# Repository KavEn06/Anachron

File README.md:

<h1 align="center">Anachron</h1>

<p align="center"><b>A smart pocket watch.</b></p>

<p align="center">
  ESP32-S3 &nbsp;·&nbsp; 1.46" round touch display &nbsp;·&nbsp; haptics &nbsp;·&nbsp; rotary crown &nbsp;·&nbsp; USB-C charging &nbsp;·&nbsp; 45 mm 4-layer PCB
</p>

Anachron is a smart pocket watch: an extension of your phone that does what a smartwatch does, but lives in your pocket instead of on your wrist. The idea comes from the same place as people going back to wired headphones.

Everything sits on one round PCB sized to match the display. An ESP32-S3 drives a 412 × 412 round touch screen, a rotary encoder with a push button behind it acts as the crown, a haptic motor gives feedback, and a LiPo cell charges over USB-C. This repository holds the electronics, designed in KiCad 10, and renders of the enclosure, modeled in Fusion 360.

## Contents

- [Concept](#concept)
- [Hardware](#hardware)
- [Why these parts](#why-these-parts)
- [The board](#the-board)
- [PCB layers](#pcb-layers)
- [Schematics](#schematics)
- [Pin map](#pin-map)
- [Power budget](#power-budget)
- [Firmware notes](#firmware-notes)
- [Bill of materials](#bill-of-materials)
- [Enclosure](#enclosure)
- [Working with the project](#working-with-the-project)

## Concept

The original sketch describes a pocket watch or keychain with several faces that connects to a phone over Bluetooth LE. The plan was for it to:

- show notifications from the phone
- control music with the crown and two programmable buttons
- work as a normal pocket watch, with the time and a timer
- switch between faces, including a Tamagotchi-style one and a CD-style one for Spotify
- use the IMU to wake up and to feed features on those faces

The shape in the sketch is the one the board follows: a round touch screen, a crown at the top with a button either side, and a USB-C port at the bottom for charging and flashing. The haptic motor, a "maybe" in the sketch, made it onto the board.

## Hardware

| Block | Part | Details |
| --- | --- | --- |
| MCU | ESP32-S3-WROOM-1-N8R8 | Dual-core 240 MHz, Wi-Fi and Bluetooth LE, 8 MB flash, 8 MB PSRAM, native USB |
| Display | Waveshare 1.46inch Touch LCD Module | Round IPS, 412 × 412, SPD2010 controller. Display over QSPI, touch over I2C (address `0x53`), on an 18-pin 0.5 mm flat-flex cable |
| Motion | Bosch BMI270 | 6-axis IMU on I2C (address `0x69`), both interrupt pins wired, used for wake and gesture detection |
| Haptics | TITAN Drake motor + MAX98357A | The I2S amplifier drives the motor through the `MP1` pads; gain is set by a solder jumper |
| Crown | Alps EC05 rotary encoder + C&K PTS845 | The encoder has no switch of its own, so a push button sits behind it in line with the shaft |
| Side buttons | 2 × C&K PTS845 | Left and right. All three buttons share one ADC pin through a resistor ladder |
| Timekeeping | 32.768 kHz crystal (Seiko SC-32S) | No separate RTC chip: the time is synced from the phone and the crystal keeps it in between |
| Charging | MCP73831 | Single-cell charger at 212 mA with a charge LED |
| Power path | AO3401A + SM5817 | Runs from USB when plugged in, from the battery otherwise |
| Regulator | AP2112K-3.3 | 600 mA, 3.3 V LDO, enabled by the `SYS PWR` solder jumper |
| USB | GCT USB4520 USB-C | USB 2.0 for flashing, with USBLC6-2SC6 ESD protection |
| Battery | 802035 LiPo, 400 to 550 mAh | Has its own protection circuit, plugs into a JST-PH connector, voltage measured through a divider |

```mermaid
flowchart LR
    USB["USB-C"] -->|VBUS| CHG["MCP73831 charger"]
    CHG --> BAT["LiPo cell"]
    USB -->|"VBUS through SM5817"| VSYS(("VSYS"))
    BAT -->|"AO3401A"| VSYS
    VSYS --> LDO["AP2112K 3.3 V"]
    LDO --> MCU["ESP32-S3-WROOM-1"]
    USB <-->|"USB data"| MCU
    MCU <-->|QSPI| LCD["1.46 inch round LCD"]
    MCU <-->|I2C| TOUCH["Touch"]
    MCU <-->|I2C| IMU["BMI270"]
    MCU -->|I2S| AMP["MAX98357A"]
    AMP --> OUT["Haptic motor"]
    ENC["Crown encoder"] --> MCU
    BTN["3 buttons"] -->|ADC| MCU
    XTAL["32.768 kHz crystal"] --- MCU
```

## Why these parts

- **Display:** the 1.46" round panel has the highest resolution and thinnest bezels of the options, and is about the size of a medium pocket watch movement.
- **MCU:** one ESP32-S3 module holds the processor, radio, memory and antenna, which is simpler and cheaper than an STM32 with a separate radio. Its 8 MB of PSRAM holds full frame buffers for the display.
- **IMU:** the BMI270 has gesture detection built in, with nothing to train.
- **Regulator:** an LDO, because the drop to 3.3 V is small and it takes less space than a switching regulator.

## The board

<p align="center">
  <b>Top</b> (left): nearly every component is on this side. <b>Bottom</b> (right): battery connector, test pads and the haptic motor pads.
</p>

| | |
| --- | --- |
| Outline | 45 mm circle, 47 mm tall including the USB-C tab and mounting ears |
| Mounting | 3 × 2.25 mm holes |
| Layers | 4 copper layers, 1.6 mm thick |
| Finish | ENIG, white solder mask, black silkscreen |
| Tracks | 0.125 mm to 0.45 mm wide, 0.1 mm minimum clearance |
| Vias | 194 through vias, 0.2 mm and 0.3 mm drills |
| Components | 57 footprints on top, 10 on the bottom |

The crown encoder sits at the top edge with its push button directly behind it and a side button on either side. The USB-C connector is recessed into a cut-out at the bottom, and the display connector is on the right. The ESP32 antenna points off the left edge, and copper is kept out from under it on all four layers.

The board is 45 mm across to match the display module, which is 44.77 mm in diameter.

### PCB artwork

The board artwork pairs flowing blue-and-white lines on the front with a distorted pocket watch on the back.

## PCB layers

<table>
  <tr>
    <td width="50%"></td>
    <td width="50%"></td>
  </tr>
  <tr>
    <td align="center"><b>Layer 1: F.Cu</b><br>Components and most routing, filled with ground.</td>
    <td align="center"><b>Layer 2: In1.Cu</b><br>Unbroken ground plane.</td>
  </tr>
  <tr>
    <td></td>
    <td></td>
  </tr>
  <tr>
    <td align="center"><b>Layer 3: In2.Cu</b><br>3.3 V plane with a VBUS island by the USB connector.</td>
    <td align="center"><b>Layer 4: B.Cu</b><br>The rest of the routing, filled with ground.</td>
  </tr>
</table>

<table>
  <tr>
    <td width="50%"></td>
    <td width="50%"></td>
  </tr>
  <tr>
    <td align="center"><b>Routing, all layers</b></td>
    <td align="center"><b>Component placement (F.Fab)</b></td>
  </tr>
</table>

## Schematics

The schematic is split into three sheets. A PDF of all of them is in [`docs/Anachron-schematic.pdf`](docs/Anachron-schematic.pdf).

### MCU and screen

### Peripherals

### Power

## Pin map

| GPIO | Net | Connects to |
| --- | --- | --- |
| EN | `RESET` | Reset button |
| IO0 | `BOOT` | Boot button |
| IO1 | `SCL` | I2C clock: touch (`0x53`), BMI270 (`0x69`) |
| IO2 | `SDA` | I2C data: touch (`0x53`), BMI270 (`0x69`) |
| IO4 | `LCD_BL` | Display backlight |
| IO5 | `TP_INT` | Touch interrupt |
| IO6 | `ADC_Button` | Button ladder |
| IO7 | `ADC_Bat` | Battery voltage divider |
| IO8 | `AMP_Mode` | MAX98357A shutdown / mode |
| IO9 | `LCD_IO3` | Display QSPI data 3 |
| IO10 | `LCD_CS` | Display chip select |
| IO11 | `LCD_IO0` | Display QSPI data 0 |
| IO12 | `LCD_SCLK` | Display QSPI clock |
| IO13 | `LCD_IO1` | Display QSPI data 1 |
| IO14 | `LCD_IO2` | Display QSPI data 2 |
| IO15, IO16 | `MCU_OSC_P`, `MCU_OSC_N` | 32.768 kHz crystal |
| IO17 | `IMU_INT1` | BMI270 interrupt 1 |
| IO18 | `IMU_INT2` | BMI270 interrupt 2 |
| IO19, IO20 | `MCU_D_N`, `MCU_D_P` | USB D−, D+ |
| IO21 | `LCD_TE` | Display tearing effect |
| IO38 | `EN_B` | Encoder channel B |
| IO39 | `EN_A` | Encoder channel A |
| IO40 | `AMP_LRCLK` | I2S word clock |
| IO41 | `AMP_BCLK` | I2S bit clock |
| IO42 | `AMP_DIN` | I2S data |
| IO43 (TXD0) | `MCU_TX` | Test pad marked `RX` |
| IO44 (RXD0) | `MCU_RX` | Test pad marked `TX` |
| IO47 | `LCD_RST` | Display reset |
| IO48 | `TP_RST` | Touch reset |

IO3, IO45 and IO46 are strapping pins and are left unconnected. IO35 to IO37 are left free because the module's PSRAM uses them. Both analog inputs (IO6 and IO7) are on ADC1, which keeps working while Wi-Fi is on.

## Power budget

The battery was sized for about 10 hours away from the charger, with the screen on for roughly 30 % of that time. These are design estimates, not measurements.

| Load | Current | Time | Charge |
| --- | --- | --- | --- |
| Backlight at full brightness | 40 to 80 mA | 3 h | 120 to 240 mAh |
| Panel and display controller | 10 mA | 3 h | 30 mAh |
| ESP32-S3 active | 30 mA | 3 h | 90 mAh |
| Bluetooth LE, average | 5 mA | 3 h | 15 mAh |
| BMI270, normal mode | 0.7 mA | 3 h | 2 mAh |
| Everything asleep | 0.25 mA | 7 h | 2 mAh |
| **Total** | | | **260 to 380 mAh** |

Taking the middle of that range and allowing for regulator losses and the part of the cell that cannot be used gives a target of about 450 mAh. The cell chosen is an 802035 LiPo, which comes in capacities from 400 to 550 mAh.

## Firmware notes

There is no firmware in this repository yet. These are the things the hardware expects from it:

- **Display.** The panel uses an SPD2010 controller over QSPI and keeps the frame in its own memory. The plan is to use LVGL for graphics. ESP-IDF's `esp_lcd` has QSPI panel drivers, and SPD2010 display and touch components are available for it.
- **IMU.** The BMI270 does nothing until an 8 KB configuration file is uploaded at boot. The likely choice is `bmi270_legacy`: it provides tap, orientation and motion detection, which run on the accelerometer alone so the ESP32 can stay asleep until an interrupt arrives.
- **Time.** The watch gets the time from the phone over Bluetooth and keeps it with the 32.768 kHz crystal while disconnected.
- **Buttons.** The three buttons are read as voltage levels on one ADC pin through a resistor ladder.
- **Flashing.** Over the USB-C port, using the ESP32-S3's built-in USB.

## Bill of materials

<details>
<summary>Show all parts</summary>

| Reference | Qty | Part | Package |
| --- | --- | --- | --- |
| U3 | 1 | ESP32-S3-WROOM-1-N8R8 | Module |
| U1 | 1 | AP2112K-3.3TRG1 | SOT-23-5 |
| U2 | 1 | MCP73831T-2ACI/OT | SOT-23-5 |
| U4 | 1 | BMI270 | LGA-14 |
| U5 | 1 | MAX98357A | TQFN-16 |
| D1 | 1 | USBLC6-2SC6 | SOT-23-6 |
| D2 | 1 | LED | 0603 |
| D3 | 1 | SM5817PL-TP | SOD-123FL |
| Q1 | 1 | AO3401A | SOT-23 |
| Y1 | 1 | Seiko SC32S-7PF20PPM, 32.768 kHz crystal | SC-32S |
| J1 | 1 | GCT USB4520-03-0-A | USB-C receptacle |
| J2 | 1 | GCT FFC2B35-18-G | 18-pin 0.5 mm FFC |
| BT1 | 1 | JST B2B-PH-K | JST-PH 2-pin |
| S1, S2 | 2 | TS18-5-25-SL-160-SMT-TR (reset, boot) | Tactile switch |
| S3, S4, S5 | 3 | C&K PTS845 (left, crown, right) | Side-actuated tactile switch |
| S6 | 1 | Alps EC05E1220401 | Rotary encoder |
| C1, C6, C9, C10, C13, C14, C15, C16, C20, C21 | 10 | 100 nF | 0603 |
| C4, C5, C8 | 3 | 1 µF | 0603 |
| C2, C3 | 2 | 4.7 µF | 0603 |
| C11, C12 | 2 | 4 pF | 0603 |
| C17 | 1 | 10 µF | 0805 |
| C7 | 1 | 22 µF | 0805 |
| R9 | 1 | 0 Ω | 0603 |
| R4 | 1 | 470 Ω | 0603 |
| R3, R13, R14 | 3 | 4.7 kΩ | 0603 |
| R1, R2 | 2 | 5.1 kΩ | 0603 |
| R5, R6, R7, R8, R15, R17, R18, R19, R20 | 9 | 10 kΩ | 0603 |
| R16 | 1 | 22 kΩ | 0603 |
| R11, R12 | 2 | 100 kΩ | 0603 |
| SW1, SW2 | 2 | Solder jumper | |
| TP1 to TP7 | 7 | Test pad, 1.5 mm | |
| MP1 | 1 | Haptic motor pads | |

</details>

Parts that connect to the board:

| Part | Connects to |
| --- | --- |
| Waveshare 1.46inch Touch LCD Module (412 × 412, SPD2010) | `J2`, 18-pin 0.5 mm flat-flex cable |
| 802035 LiPo cell with protection circuit, 400 to 550 mAh | `BT1`, JST-PH |
| TITAN Drake haptic motor | `MP1` pads |

## Enclosure

The enclosure was modeled in Fusion 360 with a satin blue anodized aluminum appearance and matte brass controls. The faces in the render at the top of this page are mockups; there is no firmware yet.

The exploded view shows the display, front housing, populated PCB, battery and rear housing in assembly order. The crown, buttons, and haptic motor are spaced out to show where they fit.

<table>
  <tr>
    <td width="50%"></td>
    <td width="50%"></td>
  </tr>
  <tr>
    <td align="center"><b>Front interior</b><br>With the display removed from view.</td>
    <td align="center"><b>Rear interior</b><br>With the back shell and battery hidden.</td>
  </tr>
</table>

The display module sets the proportions: it is 44.77 mm across and already 9.6 mm thick, where a traditional pocket watch is 9 to 15 mm in total. The case is built tightly around the display, board and battery to keep the watch as slim as that stack allows.

## Working with the project

Open `kicad/Anachron.kicad_pro` in KiCad 10. The custom symbols, footprints and 3D models are in `kicad/Library` and are referenced relative to the project, so nothing else needs installing. The [enclosure STEP files](3d%20models/) include both shell halves, the crown, and both side buttons.

```
kicad/
  Anachron.kicad_pro      project
  Anachron.kicad_sch      top-level sheet
  MCUScreen.kicad_sch     MCU, display connector, crystal, battery sense
  Peripherals.kicad_sch   buttons, encoder, amplifier, IMU
  power.kicad_sch         USB-C, charger, power path, regulator
  Anachron.kicad_pcb      board
  Library/                symbols, footprints and 3D models
3d models/                individual enclosure STEP files
docs/
  images/                 renders, layer plots and schematic images
  fusion/                 Fusion 360 renders as exported
  faces/                  pictures used on the mockup watch faces
  sketches/               hand-drawn concept sketch
  Anachron-schematic.pdf  all schematic sheets
  scripts/render_docs.py  regenerates the README images and schematic PDF
```

The PCB renders, layer plots and schematic images are generated from the KiCad files. The enclosure images are made from the Fusion 360 renders in `docs/fusion/`: the script puts them on the same dark background and builds the mockup faces shown at the top of this page, using the pictures in `docs/faces/`. To refresh everything, run the following command.

```sh
python3 docs/scripts/render_docs.py
```

To refresh only some of the images, name the groups: `3d`, `layers`, `sch` or `fusion`. For example, `python3 docs/scripts/render_docs.py fusion` redoes just the enclosure images after a new export from Fusion 360.

The script needs KiCad's `kicad-cli`, [Pillow](https://pypi.org/project/pillow/), [NumPy](https://numpy.org/), [SciPy](https://scipy.org/) and macOS.

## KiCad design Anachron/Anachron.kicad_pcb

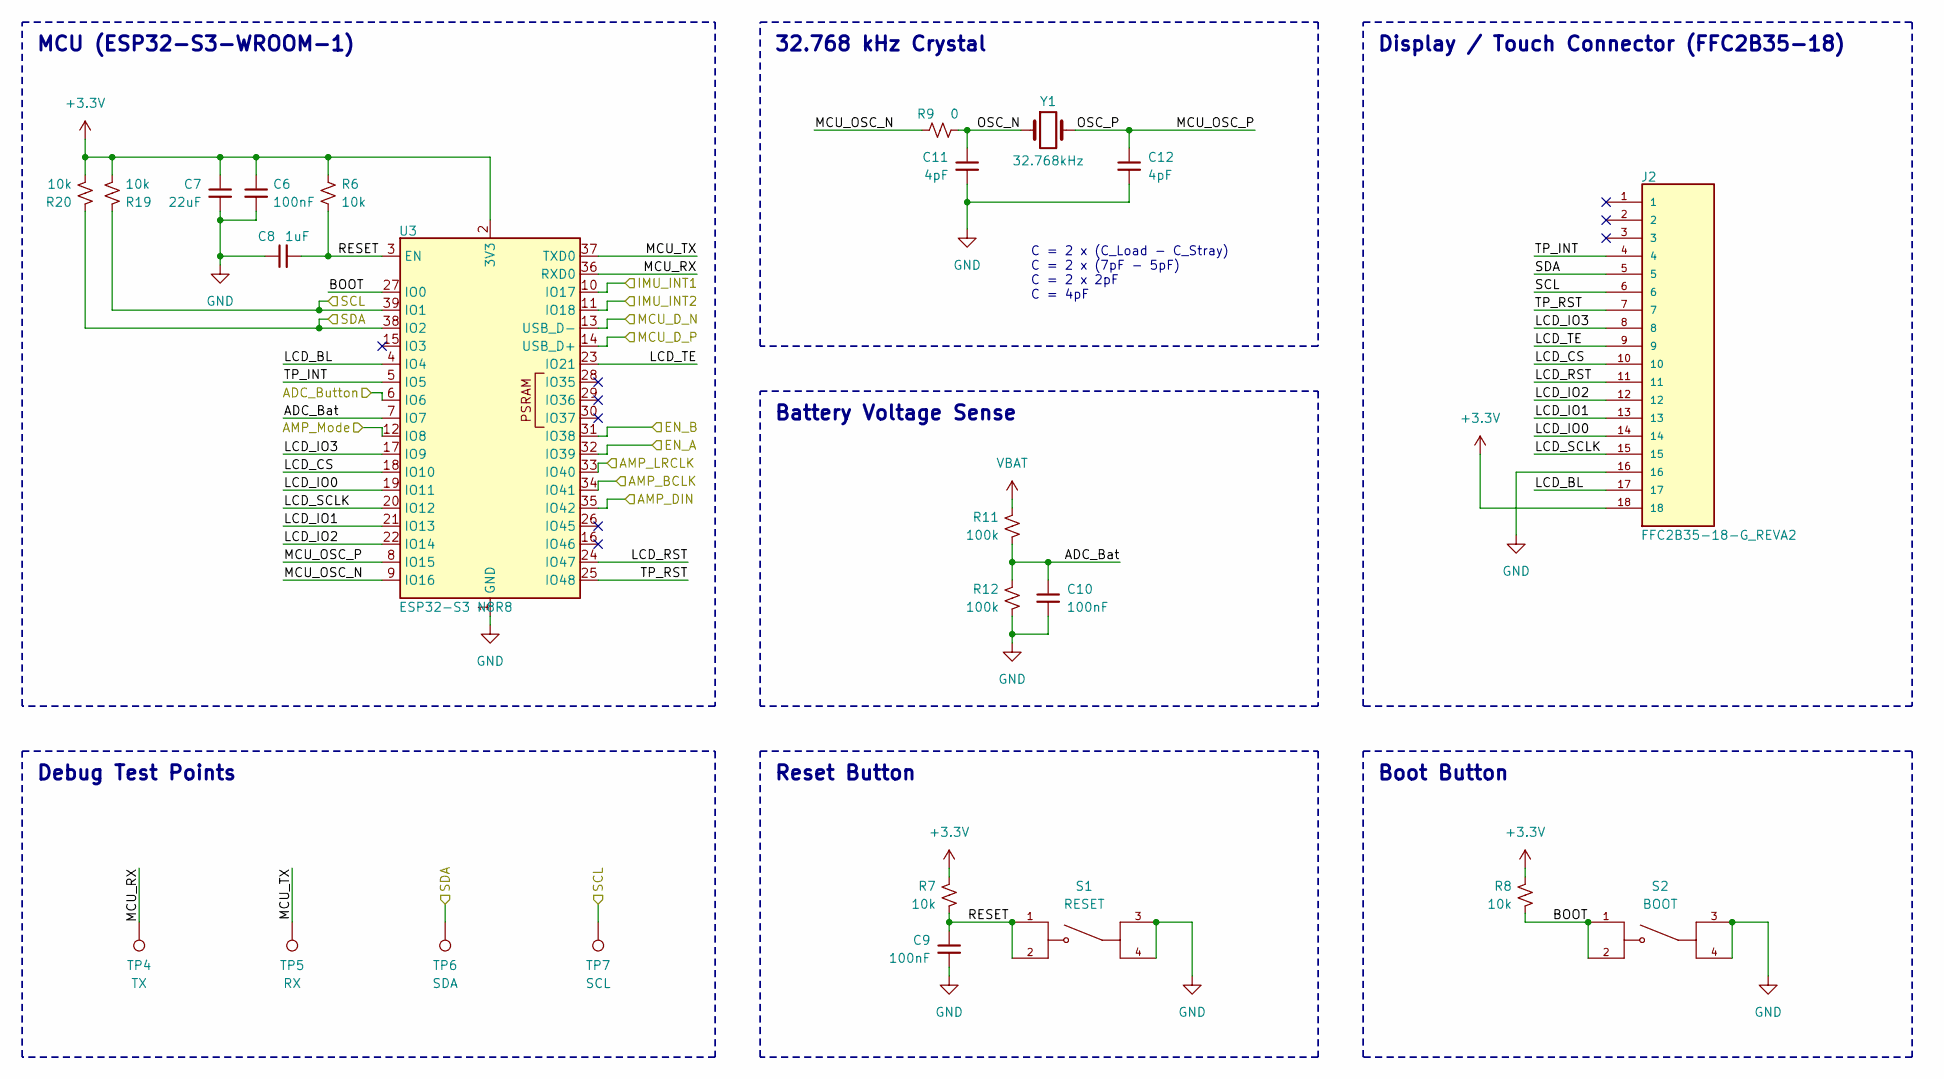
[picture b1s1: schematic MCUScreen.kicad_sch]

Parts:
C6, C9, C10: 100nF; C_0603_1608Metric
C7: 22uF; C_0805_2012Metric
C8: 1uF; C_0603_1608Metric
C11, C12: 4pF; C_0603_1608Metric
J2: FFC2B35-18-G_REVA2; GCT_FFC2B35-18-G_REVA2; PARTREV A2
R6, R7, R8, R19, R20: 10k; R_0603_1608Metric
R9: 0; R_0603_1608Metric
R11, R12: 100k; R_0603_1608Metric
S1: RESET; SW_TS18-5-25-SL-160-SMT-TR; PARTREV 1.02
S2: BOOT; SW_TS18-5-25-SL-160-SMT-TR; PARTREV 1.02
TP4: TX; TestPoint_Pad_D1.5mm
TP5: RX; TestPoint_Pad_D1.5mm
TP6: SDA; TestPoint_Pad_D1.5mm
TP7: SCL; TestPoint_Pad_D1.5mm
U3: ESP32-S3 N8R8; ESP32-S3-WROOM-1
Y1: 32.768kHz; XTAL_SC32S-7PF20PPM_EPS

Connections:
+3.3V: C6.1, C7.1, J2.18, R6.1, R7.1, R8.1, R19.2, R20.2, U3.2 (3V3); also elsewhere on the board
/MCU + Screen/ADC_Bat: C10.1, R11.2, R12.1, U3.7 (IO7)
/MCU + Screen/ADC_Button: U3.6 (IO6); also elsewhere on the board
/MCU + Screen/AMP_BCLK: U3.34 (IO41); also elsewhere on the board
/MCU + Screen/AMP_DIN: U3.35 (IO42); also elsewhere on the board
/MCU + Screen/AMP_LRCLK: U3.33 (IO40); also elsewhere on the board
/MCU + Screen/AMP_Mode: U3.12 (IO8); also elsewhere on the board
/MCU + Screen/BOOT: R8.2, S2.1, S2.2, U3.27 (IO0)
/MCU + Screen/EN_A: U3.32 (IO39); also elsewhere on the board
/MCU + Screen/EN_B: U3.31 (IO38); also elsewhere on the board
/MCU + Screen/IMU_INT1: U3.10 (IO17); also elsewhere on the board
/MCU + Screen/IMU_INT2: U3.11 (IO18); also elsewhere on the board
/MCU + Screen/LCD_BL: J2.17, U3.4 (IO4)
/MCU + Screen/LCD_CS: J2.10, U3.18 (IO10)
/MCU + Screen/LCD_IO0: J2.14, U3.19 (IO11)
/MCU + Screen/LCD_IO1: J2.13, U3.21 (IO13)
/MCU + Screen/LCD_IO2: J2.12, U3.22 (IO14)
/MCU + Screen/LCD_IO3: J2.8, U3.17 (IO9)
/MCU + Screen/LCD_RST: J2.11, U3.24 (IO47)
/MCU + Screen/LCD_SCLK: J2.15, U3.20 (IO12)
/MCU + Screen/LCD_TE: J2.9, U3.23 (IO21)
/MCU + Screen/MCU_D_N: U3.13 (USB_D-); also elsewhere on the board
/MCU + Screen/MCU_D_P: U3.14 (USB_D+); also elsewhere on the board
/MCU + Screen/MCU_OSC_N: R9.2, U3.9 (IO16)
/MCU + Screen/MCU_OSC_P: C12.1, U3.8 (IO15), Y1.2
/MCU + Screen/MCU_RX: TP4.1 (1_1), U3.36 (RXD0)
/MCU + Screen/MCU_TX: TP5.1 (1_1), U3.37 (TXD0)
/MCU + Screen/OSC_N: C11.1, R9.1, Y1.1
/MCU + Screen/RESET: C8.2, C9.1, R6.2, R7.2, S1.1, S1.2, U3.3 (EN)
/MCU + Screen/SCL: J2.6, R19.1, TP7.1 (1_1), U3.39 (IO1); also elsewhere on the board
/MCU + Screen/SDA: J2.5, R20.1, TP6.1 (1_1), U3.38 (IO2); also elsewhere on the board
/MCU + Screen/TP_INT: J2.4, U3.5 (IO5)
/MCU + Screen/TP_RST: J2.7, U3.25 (IO48)
GND: C6.2, C7.2, C8.1, C9.2, C10.2, C11.2, C12.2, J2.16, R12.2, S1.3, S1.4, S2.3, S2.4, U3.1 (GND), U3.40 (GND), U3.41 (GND); also elsewhere on the board
VBAT: R11.1; also elsewhere on the board

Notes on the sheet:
Battery Voltage Sense
Display / Touch Connector (FFC2B35-18)
Debug Test Points
Reset Button
Boot Button
32.768 kHz Crystal
MCU (ESP32-S3-WROOM-1)
C = 2 x (C_Load - C_Stray) C = 2 x (7pF - 5pF) C = 2 x 2pF C = 4pF

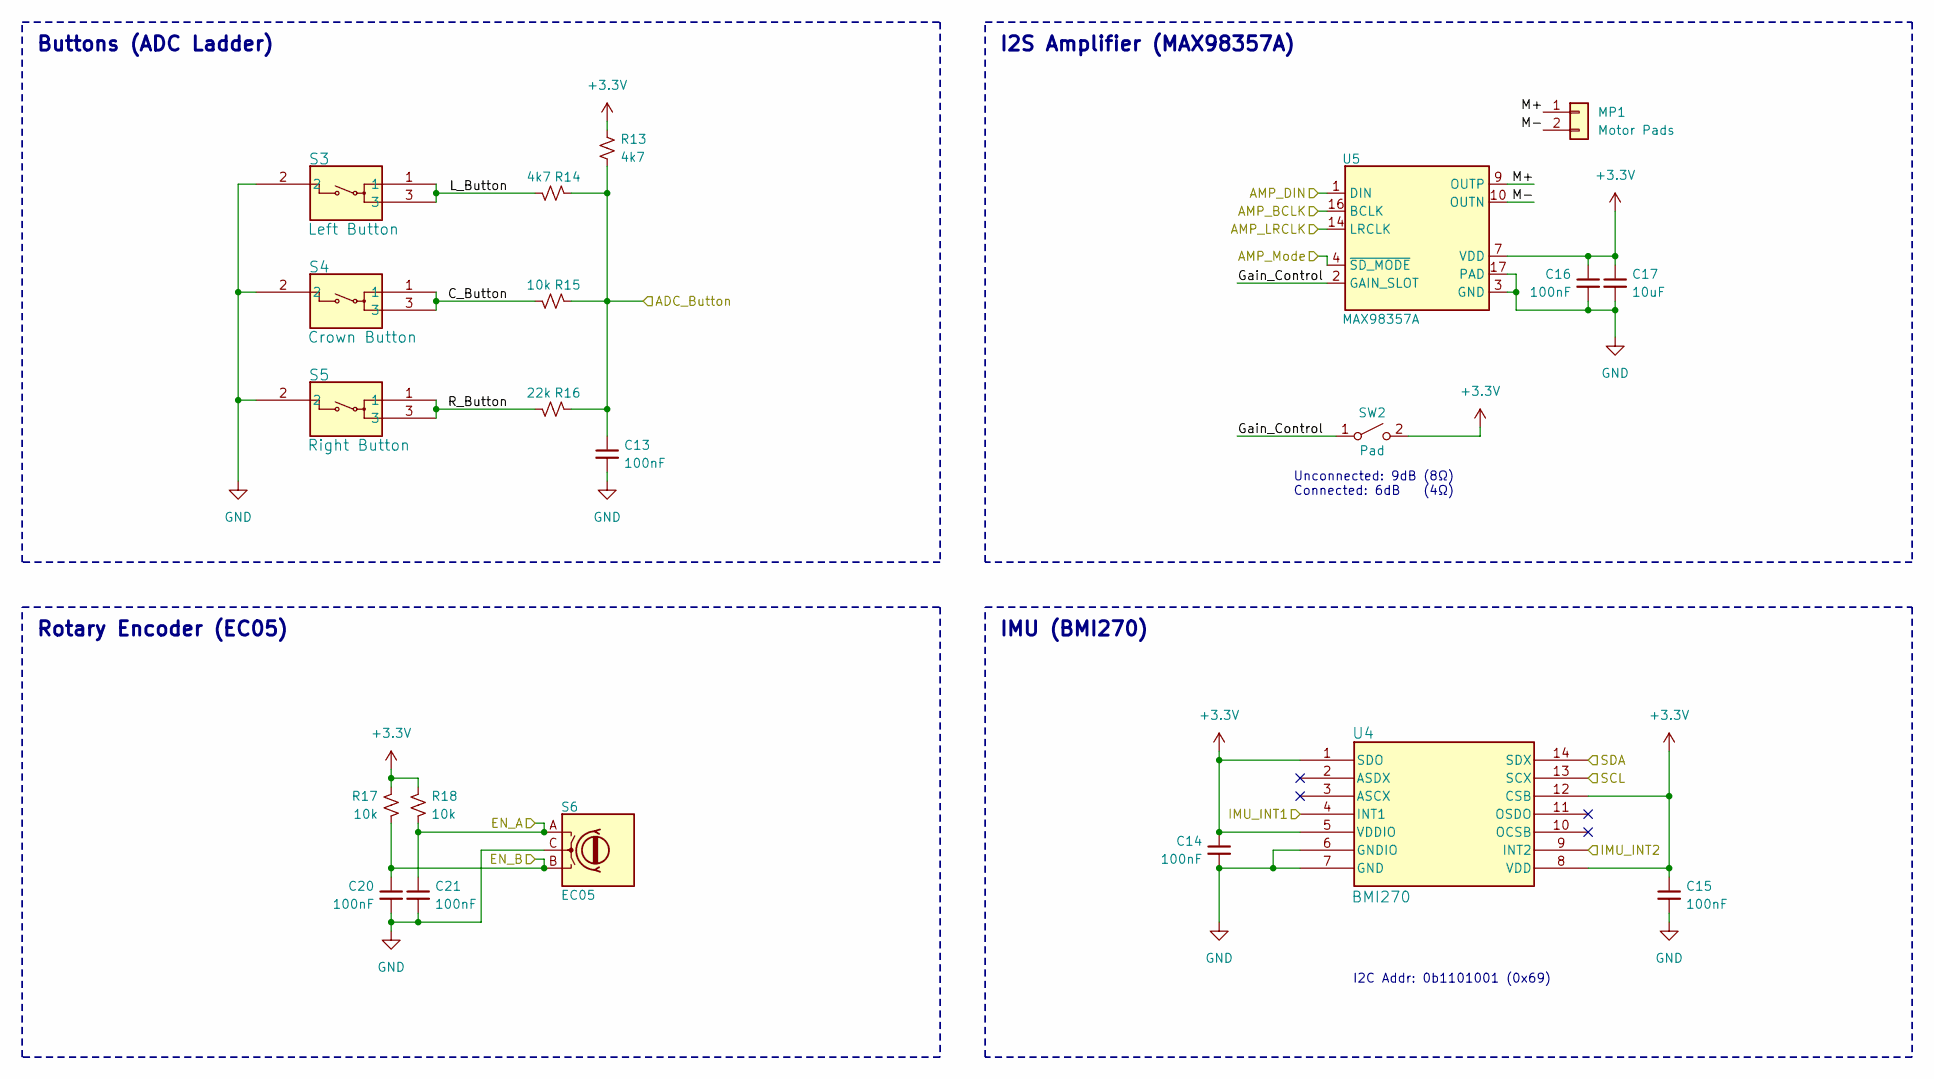
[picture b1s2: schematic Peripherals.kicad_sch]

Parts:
C13, C14, C15, C16, C20, C21: 100nF; C_0603_1608Metric
C17: 10uF; C_0805_2012Metric
MP1: Motor Pads
R13, R14: 4k7; R_0603_1608Metric
R15, R17, R18: 10k; R_0603_1608Metric
R16: 22k; R_0603_1608Metric
S3: Left Button; PTS845_CNK
S4: Crown Button; PTS845_CNK
S5: Right Button; PTS845_CNK
S6: EC05; EC05 Encoder
SW2: Pad; SolderJumper-2_P1.3mm_Open_RoundedPad1.0x1.5mm
U4: BMI270; BMI270_BOS-M
U5: MAX98357A; TQFN-16-1EP_3x3mm_P0.5mm_EP1.23x1.23mm_ThermalVias

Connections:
+3.3V: C14.1, C15.1, C16.1, C17.1, R13.1, R17.1, R18.1, SW2.2 (B), U4.1 (SDO), U4.5 (VDDIO), U4.8 (VDD), U4.12 (CSB), U5.7 (VDD), U5.8 (VDD); also elsewhere on the board
/MCU + Screen/ADC_Button: C13.1, R13.2, R14.2, R15.2, R16.2; also elsewhere on the board
/MCU + Screen/AMP_BCLK: U5.16 (BCLK); also elsewhere on the board
/MCU + Screen/AMP_DIN: U5.1 (DIN); also elsewhere on the board
/MCU + Screen/AMP_LRCLK: U5.14 (LRCLK); also elsewhere on the board
/MCU + Screen/AMP_Mode: U5.4 (~SD_MODE); also elsewhere on the board
/MCU + Screen/EN_A: C21.1, R18.2, S6.A; also elsewhere on the board
/MCU + Screen/EN_B: C20.1, R17.2, S6.B; also elsewhere on the board
/MCU + Screen/IMU_INT1: U4.4 (INT1); also elsewhere on the board
/MCU + Screen/IMU_INT2: U4.9 (INT2); also elsewhere on the board
/MCU + Screen/SCL: U4.13 (SCX); also elsewhere on the board
/MCU + Screen/SDA: U4.14 (SDX); also elsewhere on the board
/Peripherals/C_Button: R15.1, S4.1, S4.3
/Peripherals/Gain_Control: SW2.1 (A), U5.2 (GAIN_SLOT)
/Peripherals/L_Button: R14.1, S3.1, S3.3
/Peripherals/M+: MP1.1, U5.9 (OUTP)
/Peripherals/M-: MP1.2, U5.10 (OUTN)
/Peripherals/R_Button: R16.1, S5.1, S5.3
GND: C13.2, C14.2, C15.2, C16.2, C17.2, C20.2, C21.2, S3.2, S4.2, S5.2, S6.C, U4.6 (GNDIO), U4.7 (GND), U5.3 (GND), U5.11 (GND), U5.15 (GND), U5.17 (PAD); also elsewhere on the board

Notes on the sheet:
Rotary Encoder (EC05)
I2S Amplifier (MAX98357A)
Unconnected: 9dB Connected: 6dB
Buttons (ADC Ladder)
IMU (BMI270)
I2C Addr: 0b1101001 (0x69)
(8Ω) (4Ω)

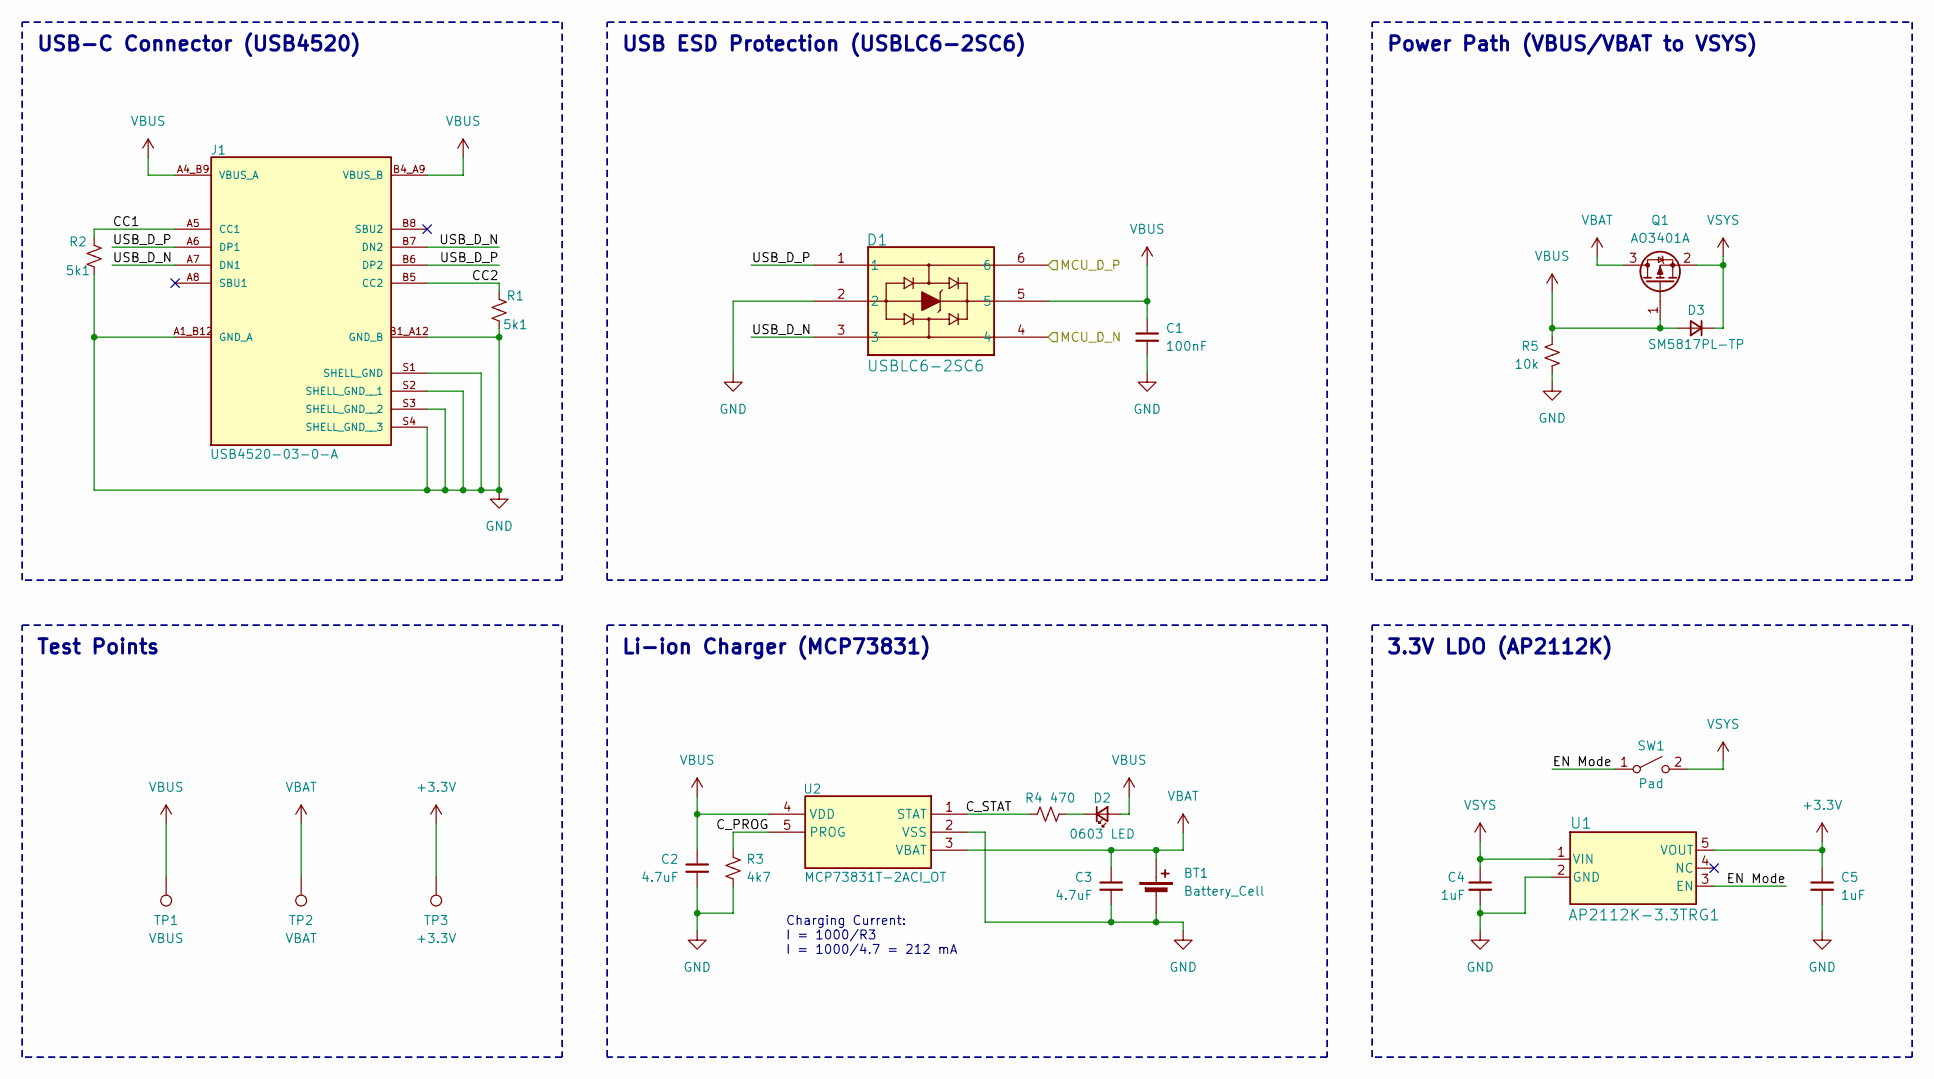
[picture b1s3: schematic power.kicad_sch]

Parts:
BT1: Battery_Cell; JST_PH_B2B-PH-K_1x02_P2.00mm_Vertical
C1: 100nF; C_0603_1608Metric
C2, C3: 4.7uF; C_0603_1608Metric
C4, C5: 1uF; C_0603_1608Metric
D1: USBLC6-2SC6; SOT23-6L_STM
D2: 0603 LED; LED_0603_1608Metric
D3: SM5817PL-TP; CR_5817PL-TP_MCC
J1: USB4520-03-0-A; GCT_USB4520-03-0-A_REVA; PARTREV A
Q1: AO3401A; SOT-23
R1, R2: 5k1; R_0603_1608Metric
R3: 4k7; R_0603_1608Metric
R4: 470; R_0603_1608Metric
R5: 10k; C_0603_1608Metric
SW1: Pad; SolderJumper-2_P1.3mm_Open_RoundedPad1.0x1.5mm
TP1: VBUS; TestPoint_Pad_D1.5mm
TP2: VBAT; TestPoint_Pad_D1.5mm
TP3: +3.3V; TestPoint_Pad_D1.5mm
U1: AP2112K-3.3TRG1; SOT_RG1_DIO
U2: MCP73831T-2ACI_OT; SOT95P270X145-5N; Mouser Part Number 579-MCP73831T-2ACIOT

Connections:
+3.3V: C5.1, TP3.1 (1_1), U1.5 (VOUT); also elsewhere on the board
/MCU + Screen/MCU_D_N: D1.4; also elsewhere on the board
/MCU + Screen/MCU_D_P: D1.6; also elsewhere on the board
/Power/CC1: J1.A5 (CC1), R2.1
/Power/CC2: J1.B5 (CC2), R1.1
/Power/C_PROG: R3.1, U2.5 (PROG)
/Power/C_STAT: R4.2, U2.1 (STAT)
/Power/EN Mode: SW1.1 (A), U1.3 (EN)
/Power/USB_D_N: D1.3, J1.A7 (DN1), J1.B7 (DN2)
/Power/USB_D_P: D1.1, J1.A6 (DP1), J1.B6 (DP2)
GND: BT1.2 (-), C1.2, C2.2, C3.2, C4.2, C5.2, D1.2, J1.A1_B12 (GND_A), J1.B1_A12 (GND_B), J1.S1 (SHELL_GND), J1.S2 (SHELL_GND__1), J1.S3 (SHELL_GND__2), J1.S4 (SHELL_GND__3), R1.2, R2.2, R3.2, R5.2, U1.2 (GND), U2.2 (VSS); also elsewhere on the board
unnamed: D2.1 (K), R4.1
VBAT: BT1.1 (+), C3.1, Q1.3 (D), TP2.1 (1_1), U2.3 (VBAT); also elsewhere on the board
VBUS: C1.1, C2.1, D1.5, D2.2 (A), D3.2 (A), J1.A4_B9 (VBUS_A), J1.B4_A9 (VBUS_B), Q1.1 (G), R5.1, TP1.1 (1_1), U2.4 (VDD)
VSYS: C4.1, D3.1 (K), Q1.2 (S), SW1.2 (B), U1.1 (VIN)

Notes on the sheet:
Li-ion Charger (MCP73831)
Power Path (VBUS/VBAT to VSYS)
USB-C Connector (USB4520)
Charging Current: I = 1000/R3 I = 1000/4.7 = 212 mA
3.3V LDO (AP2112K)
USB ESD Protection (USBLC6-2SC6)
Test Points

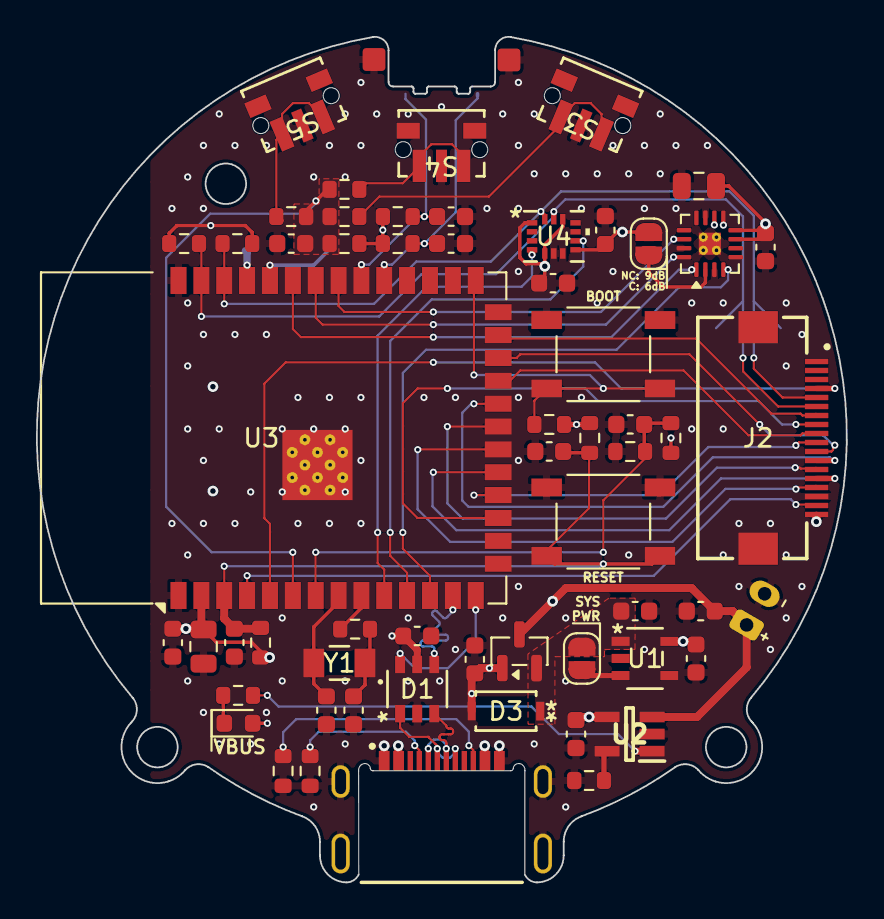
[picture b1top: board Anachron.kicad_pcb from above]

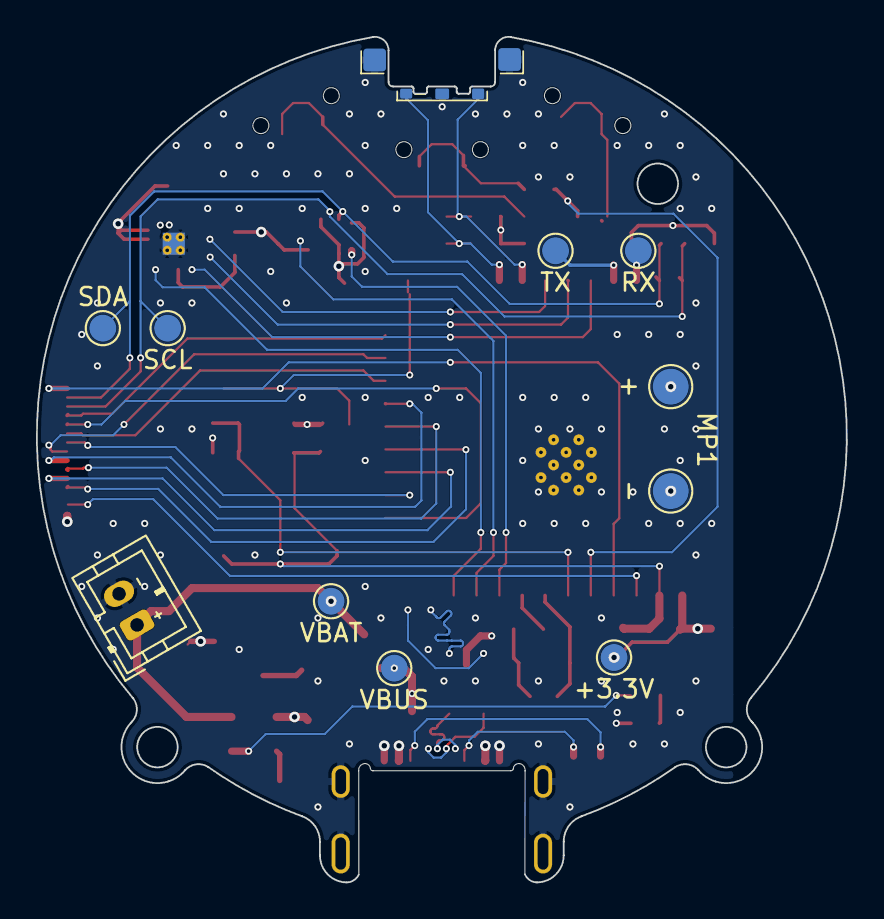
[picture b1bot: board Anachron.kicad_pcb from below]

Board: 4 copper layers, 45.0 x 47.0 mm, 67 parts (10 on the bottom side), 51 nets.
